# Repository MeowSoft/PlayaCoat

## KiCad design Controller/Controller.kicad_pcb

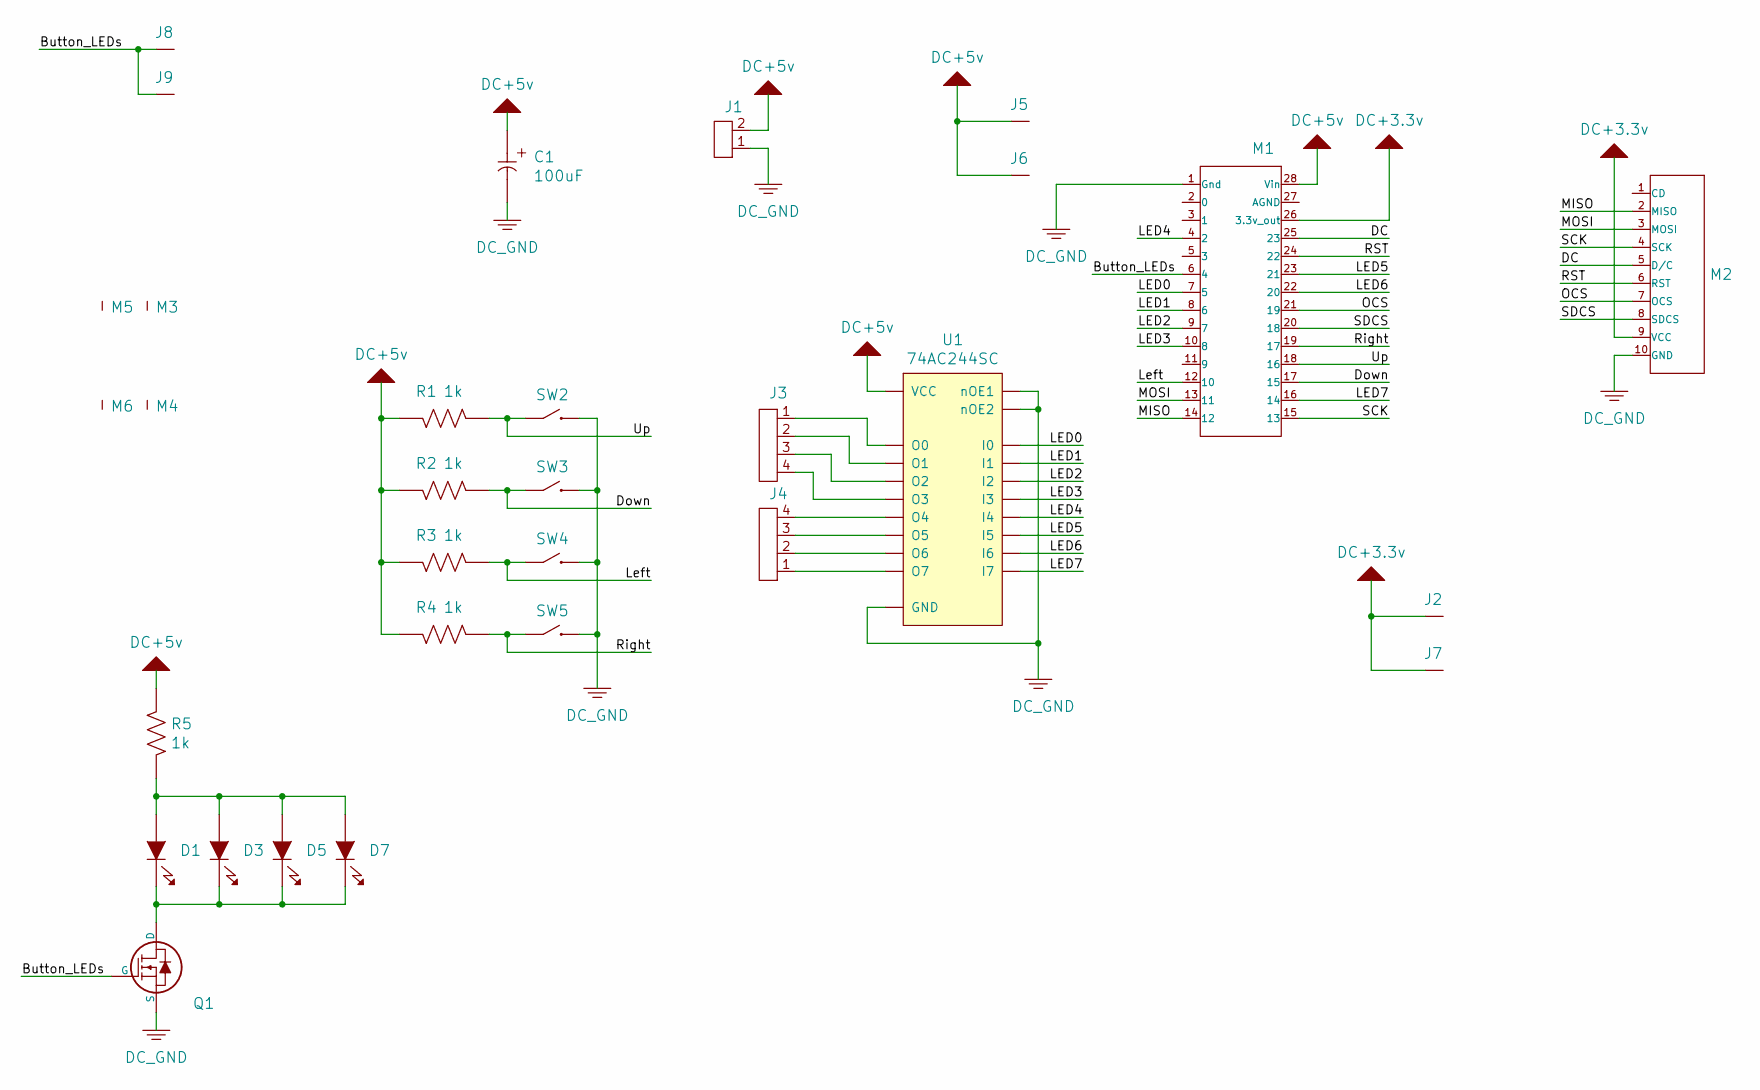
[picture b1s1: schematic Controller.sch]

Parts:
C1: 0000100000000_100uF_UWX1C101MCL1GB; 8mmx6.5mm; Voltage 16VDC; Tolerance +-20%; Mfr PN UWX1C101MCL1GB
D1, D3, D5, D7: Lumex_SSL-LX3T453GD; Mfr PN SSL-LX3T453GD
J1: 0002_2-Position-RA_43650-0212; 43650-0212; Mfr PN 43650-0212
J2, J5, J6, J7, J8, J9: Wire_Pad_01; Solder_Pad_ThroughHole_45mil
J3, J4: 0004_4-Position-RA_43650-0412; 43650-0412; Mfr PN 43650-0412
M1: PCB-Module_PJRC_Teensy_3.2; PJRC_Teensy_3.2
M2: PCB-Module_Adafruit_096_OLED_Display; Adafruit_0.96_OLED_Display
M3, M4, M5, M6: No4_Screw_Mount; Mfr PN NA
Q1: ROHM_RK7002BMT116; SOT-23-3; Mfr PN RK7002BMT116
R1, R2, R3, R4, R5: 00001000000_1k_MC0805WAF1001T5E-TC; 0805; Tolerance 1%; Mfr PN MC0805WAF1001T5E-TC
SW2, SW3, SW4, SW5: Omron_B3F-1000; Omron_B3F-100x; Mfr PN B3F-1000
U1: Fairchild_74AC244SC; SOIC-20-Wide; Mfr PN 74AC244SC

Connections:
+3.3V: J2.1, J7.1, M1.26 (3.3v_out), M2.9 (VCC)
+5V: C1.1 (A), J1.2, J5.1, J6.1, M1.28 (Vin), R1.1, R2.1, R3.1, R4.1, R5.1, U1.20 (VCC)
/Button_LEDs: J8.1, J9.1, M1.6 (4), Q1.1 (G)
/DC: M1.25 (23), M2.5 (D/C)
/Down: M1.17 (15), R2.2, SW3.3 (C2), SW3.4
/LED0: M1.7 (5), U1.2 (I0)
/LED1: M1.8 (6), U1.4 (I1)
/LED2: M1.9 (7), U1.6 (I2)
/LED3: M1.10 (8), U1.8 (I3)
/LED4: M1.4 (2), U1.17 (I4)
/LED5: M1.23 (21), U1.15 (I5)
/LED6: M1.22 (20), U1.13 (I6)
/LED7: M1.16 (14), U1.11 (I7)
/Left: M1.12 (10), R3.2, SW4.3 (C2), SW4.4
/MISO: M1.14 (12), M2.2 (MISO)
/MOSI: M1.13 (11), M2.3 (MOSI)
/OCS: M1.21 (19), M2.7 (OCS)
/RST: M1.24 (22), M2.6 (RST)
/Right: M1.19 (17), R4.2, SW5.3 (C2), SW5.4
/SCK: M1.15 (13), M2.4 (SCK)
/SDCS: M1.20 (18), M2.8 (SDCS)
/Up: M1.18 (16), R1.2, SW2.3 (C2), SW2.4
DC_GND: C1.2 (C), J1.1, J1.5, J1.6, J3.5, J3.6, J4.5, J4.6, M1.1 (Gnd), M2.10 (GND), Q1.2 (S), SW2.1 (C1), SW2.2, SW3.1 (C1), SW3.2, SW4.1 (C1), SW4.2, SW5.1 (C1), SW5.2, U1.1 (nOE1), U1.10 (GND), U1.19 (nOE2)
unnamed: D1.1 (C), D3.1 (C), D5.1 (C), D7.1 (C), Q1.3 (D)
unnamed: D1.2 (A), D3.2 (A), D5.2 (A), D7.2 (A), R5.2
unnamed: J3.1, U1.18 (O0)
unnamed: J3.2, U1.16 (O1)
unnamed: J3.3, U1.14 (O2)
unnamed: J3.4, U1.12 (O3)
unnamed: J4.1, U1.9 (O7)
unnamed: J4.2, U1.7 (O6)
unnamed: J4.3, U1.5 (O5)
unnamed: J4.4, U1.3 (O4)

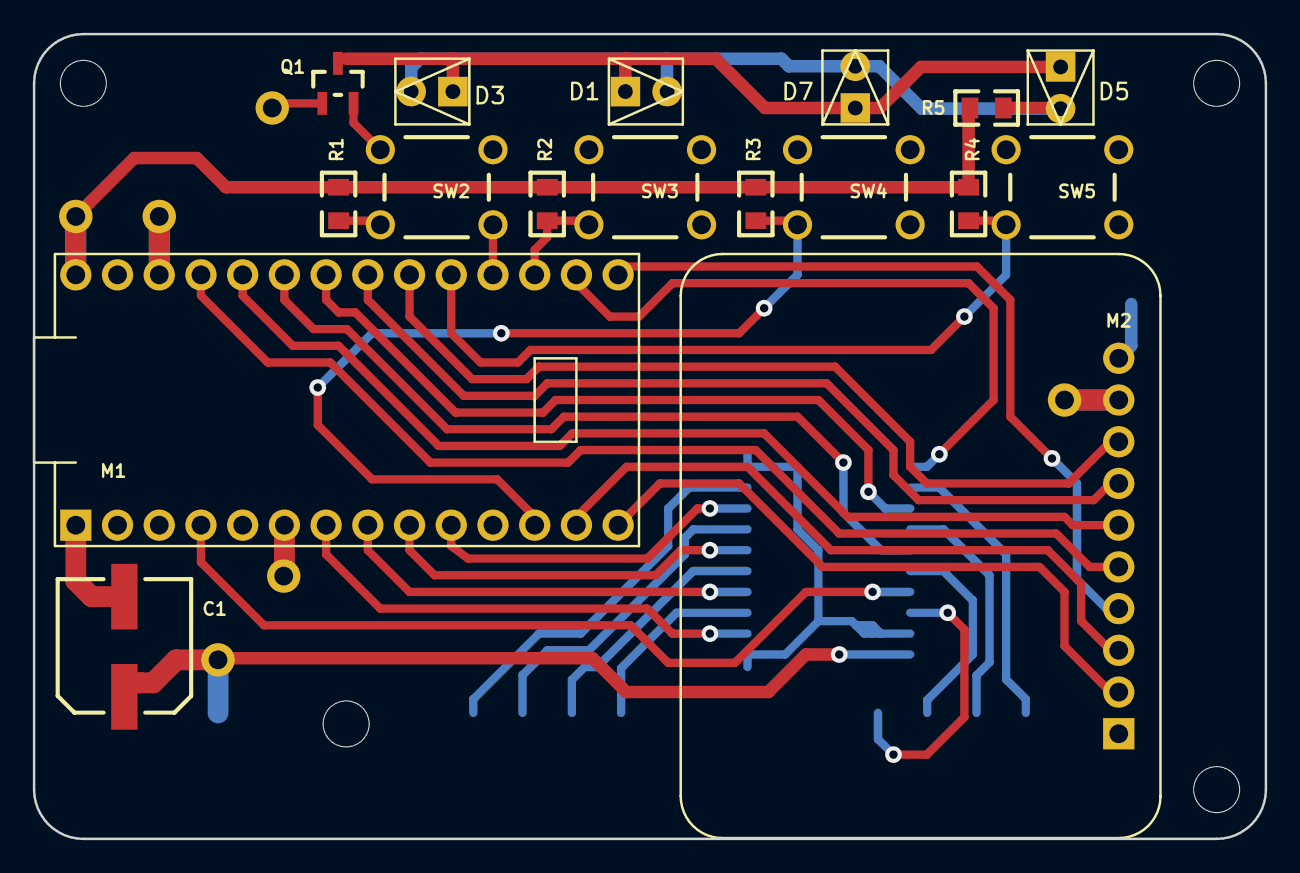
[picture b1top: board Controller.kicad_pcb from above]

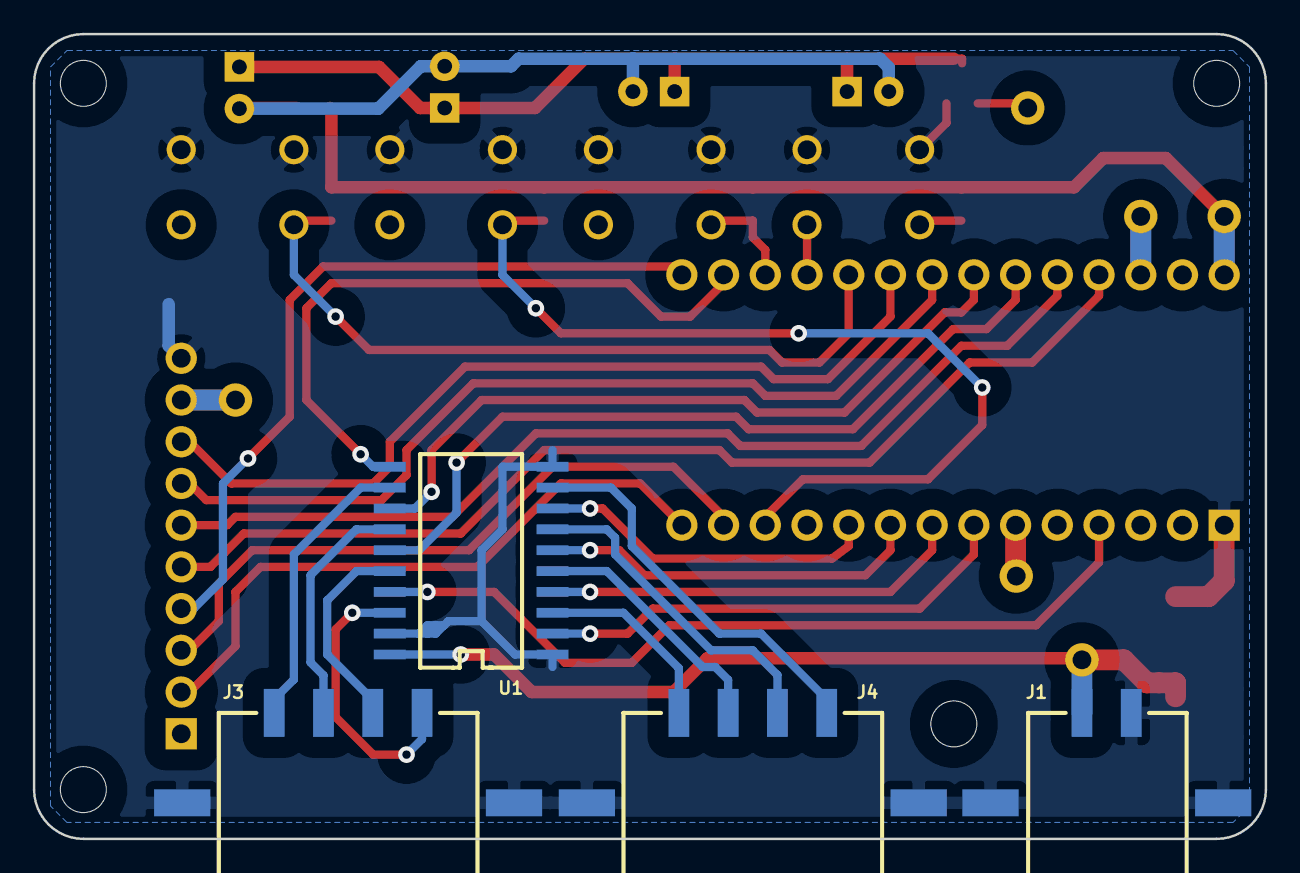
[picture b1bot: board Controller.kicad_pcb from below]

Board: 2 copper layers, 75.0 x 49.0 mm, 31 parts (4 on the bottom side), 33 nets.

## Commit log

2019-08-04 Repo created
2019-08-23 Adding controller Source
2019-08-23 Adding random function.
2019-08-23 adding rainbow
2019-08-24 adding rainbow rand function
2020-09-01 workspace
2020-10-13 Working
2020-10-14 Reorganizing oled lib.
